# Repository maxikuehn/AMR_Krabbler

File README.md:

<div align="right">

</div>

<div align="center">

<h1>Technische Optimierungen am vierbeinigen Krabbler</h1>

<h3>Autonome Mobile Roboter - SS 2024</h3>
<h4>Maximilian Kühn</h4>

</div>

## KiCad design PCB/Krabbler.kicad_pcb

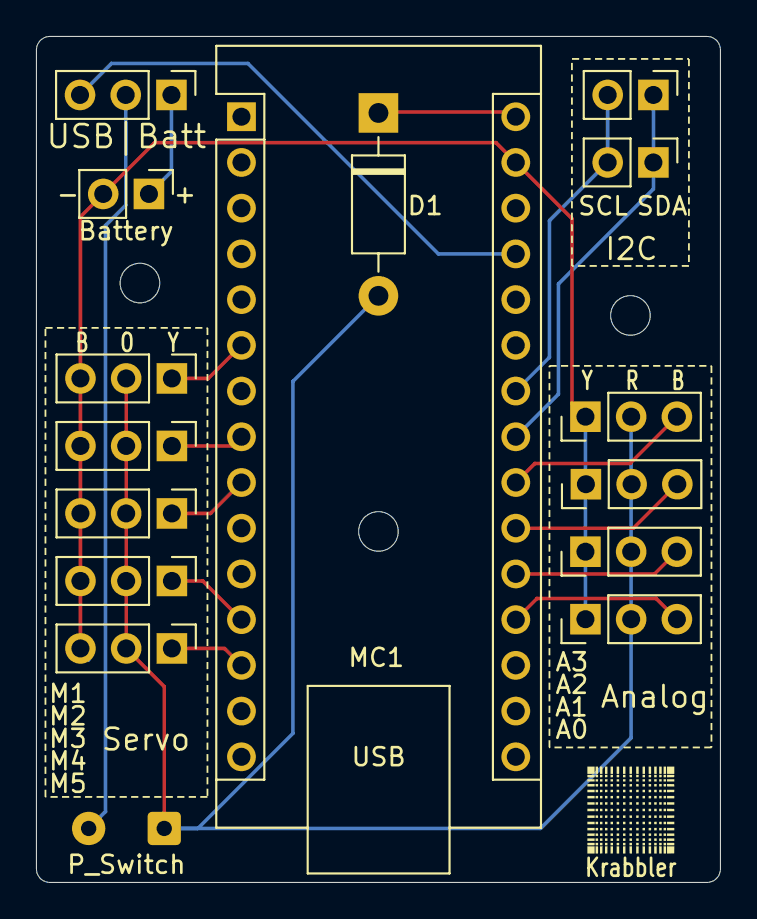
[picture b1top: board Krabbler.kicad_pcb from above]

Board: 2 copper layers, 38.0 x 47.0 mm, 16 parts (0 on the bottom side), 16 nets.

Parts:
A1: Analog_A0; PinHeader_1x03_P2.54mm_Vertical
A2: Analog_A1; PinHeader_1x03_P2.54mm_Vertical
A3: Analog_A2; PinHeader_1x03_P2.54mm_Vertical
A4: Analog_A3; PinHeader_1x03_P2.54mm_Vertical
D1: Diode; D_DO-41_SOD81_P10.16mm_Horizontal
I1: I2C_Pinout_1; PinHeader_1x02_P2.54mm_Vertical
I2: I2C_Pinout_2; PinHeader_1x02_P2.54mm_Vertical
M1: Servo_Head; PinHeader_1x03_P2.54mm_Vertical
M2: Servo_Front_Left; PinHeader_1x03_P2.54mm_Vertical
M3: Servo_Front_Right; PinHeader_1x03_P2.54mm_Vertical
M4: Servo_Back_Left; PinHeader_1x03_P2.54mm_Vertical
M5: Servo_Back_Right; PinHeader_1x03_P2.54mm_Vertical
MC1: Arduino_Nano_v3.3; Arduino_Nano
P1: Power_Jumper; PinHeader_1x03_P2.54mm_Vertical
P2: Power_Switch; SolderWire-0.25sqmm_1x02_P4.2mm_D0.65mm_OD1.7mm
P3: Battery_Pin; PinHeader_1x02_P2.54mm_Vertical

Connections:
+6V: P1.1 (-), P3.1
unnamed: A1.2 (+), A2.2 (+), A3.2 (+), A4.2 (+), D1.2 (A), M1.2 (+), M2.2 (+), M3.2 (+), M4.2 (+), M5.2 (+), P2.1
unnamed: A1.1 (-), A2.1 (-), A3.1 (-), A4.1 (-), M1.3 (-), M2.3 (-), M3.3 (-), M4.3 (-), M5.3 (-), MC1.29 (GND), P3.2
unnamed: A1.3 (data), MC1.19 (A0)
unnamed: A2.3 (data), MC1.20 (A1)
unnamed: A3.3 (data), MC1.21 (A2)
unnamed: A4.3 (data), MC1.22 (A3)
unnamed: D1.1 (K), MC1.30 (VIN)
unnamed: I1.1 (SDA), I2.1 (SDA), MC1.23 (A4)
unnamed: M1.1 (PWM), MC1.6 (D3)
unnamed: M2.1 (PWM), MC1.8 (D5)
unnamed: M3.1 (PWM), MC1.9 (D6)
unnamed: M4.1 (PWM), MC1.12 (D9)
unnamed: M5.1 (PWM), MC1.13 (D10)
unnamed: MC1.27 (+5V), P1.3 (data)
unnamed: P1.2 (+), P2.2

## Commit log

2024-07-31 update platformio deps
2024-07-31 cad init
2024-07-31 added Projektbericht
2024-12-23 Create LICENSE
